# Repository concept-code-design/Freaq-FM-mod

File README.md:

# An interpretation of the Meebleeps / Wirehead Freaq FM Synth
## Arduino Synth with Dual-voice 2-OP FM | Generative 2-track Polymetric Sequencer | Mozzi SDK

## NOTE This code is an open-source prototype and is not compatible with the Wirehead Instruments version of Freaq FM hardware
- Meebleeps was rebranded as Wirehead Instruments in 2023 to avoid brand confusion with MeeBlip - another completely separate synth design company.

This interpretation is based on https://github.com/Meebleeps/MeeBleeps-Freaq-FM-Synth

It uses a different PCB with slightly different layout. It features dual independent 2-operator FM voices paired with a 2-track generative sequencer.  

Each voice has independent carrier & modulator waveforms, FM ratio, modulation envelope & LFO.

Both tracks share the a single pattern (inspired by the Intellijel Metropolix) and can be stacked in unison or have different polymetric step-counts.  Track 1 can be offset 0-3 octaves above track 2 for separate bass & lead.

The code was addressed by Claude to match my hardware. It now also includes working MIDI out.

 #### Source Code:      https://github.com/Meebleeps/MeeBleeps-Freaq-FM-Synth
 #### Youtube Demo:     https://www.youtube.com/watch?v=KD6IrcmMkoA
 #### Youtube Channel:  https://www.youtube.com/channel/UC4I1ExnOpH_GjNtm7ZdWeWA

Source released under Creative Commons Attribution-NonCommercial-ShareAlike 4.0
Copyright (C) 2026 Concept & Code

***

## Important build-notes 

- My pcb has normally-open switches
- Work and Compile PlatformIO (I use VSCodium)). 

***

## Voices

-   2 independent FM voices
-   2-operator FM (for old-school prince of persia vibes! 😂)
-   Multi-mode FM ratios - quantised, free-multiple, independent
-   Multiple operator waveforms for carrier & modulator - Sine, Saw, Reverse Saw, Square, Noise, Off
-   Modulation level controlled by Attack/Decay envelope and LFO per-voice
-   Multiple LFO waveforms (same tables as the carrier oscillators) Sine, Saw, Reverse Saw, Square, Noise

## Sequencer

-   2/1.5 track polymetric sequencer with up to 16 steps per track (Both tracks use same note sequence but can have different step-counts for polymetric phasing)
-   Multiple generative algorithms - (semi)random notes, (semi)random runs, arpeggio, drone 
-   Sequence mutates/evolves at user-defined rate & note-density
-   Selectable tonic, octave & scale quantisation (Major, Minor, Pentatonic, Phrygian (GOA!), Octaves, Fifths)
-   Tap-tempo control
-   Sync input & output (Korg Volca compatible) 
-   16-step parameter-lock recording of synth parameters for track 1 (the Elektron way!)

## Hardware 
-   Arduino Nano (Elegoo) 
-   8x8 LED display with a MAX7219-based control board
-   Simple Mozzi output circuit 
-   Added power filtering caps on DC input and 5V rail
-   Designed to fit into Volca form factor 
-   Laser-cut metalisized acrylic faceplate 
-   Laser-cut wooden enclosure 
-   7V-12DC DC Power input 
-   Access to nano's USB port for firmware upgrades 

## Pins

These are the defaults in the original software:

| Pin | Function   | Name in `MutantFMSynth.ino` |
| --- | ---------- | --------------------------- |
| A0  | Mutation   | ANALOG_INPUT_MUTATION       |
| A1  | Wobble     | ANALOG_INPUT_LFO            |
| A2  | Population | ANALOG_INPUT_STEPCOUNT      |
| A3  | Attack     | ANALOG_INPUT_MOD_ENVELOPE2  |
| A4  | Lifespan   | ANALOG_INPUT_DECAY          |
| A5  | Decay      | ANALOG_INPUT_MOD_ENVELOPE1  |
| A6  | Ratio      | ANALOG_INPUT_MOD_RATIO      |
| A7  | Depth      | ANALOG_INPUT_MOD_AMOUNT     |
| D3  | Start      | BUTTON_INPUT_START          |
| D4  | Voice      | BUTTON_INPUT_VOICE          |
| D5  | Rec        | BUTTON_INPUT_REC            |
| D6  | Scales     | BUTTON_INPUT_SCALE          |
| D10 | Func       | BUTTON_INPUT_FUNC           |
| D12 | Tonic      | BUTTON_INPUT_TONIC          |

My hardware version (Romix panel)

The firmware in `src/` is configured for this panel. Knob functions are `primary / [FUNC] held`.

| Pin | Panel label            | Name in `MutantFMSynth.ino`  |
| --- | ---------------------- | ---------------------------- |
| A0  | MUTATION / density     | ANALOG_INPUT_MUTATION        |
| A1  | ATTACK / carrier       | ANALOG_INPUT_MOD_ENVELOPE2   |
| A2  | AMP DECAY / octave     | ANALOG_INPUT_DECAY           |
| A3  | SEQ LENGTH             | ANALOG_INPUT_STEPCOUNT       |
| A4  | DECAY / mod            | ANALOG_INPUT_MOD_ENVELOPE1   |
| A5  | FM RATIO / mode        | ANALOG_INPUT_MOD_RATIO       |
| A6  | DEPTH / lfo            | ANALOG_INPUT_MOD_AMOUNT      |
| A7  | LFO DEPTH / lfo rate   | ANALOG_INPUT_LFO             |
| D12 | Start                  | BUTTON_INPUT_START           |
| D5  | Voice                  | BUTTON_INPUT_VOICE           |
| D4  | Rec                    | BUTTON_INPUT_REC             |
| D10 | Scale                  | BUTTON_INPUT_SCALE           |
| D3  | Func                   | BUTTON_INPUT_FUNC            |
| D6  | Algo                   | BUTTON_INPUT_ALGO            |

Hardware notes:

- The switches are normally open and short their pin to GND (`SWITCH_TYPE_NORMALLY_CLOSED` is off in `MutantFMSynthOptions.h`).
- D10 (Scale) and D12 (Start) are the ATmega328's hardware SPI SS and MISO pins. With the SPI enabled, a Scale press drops it into slave mode and the Start LED can't be driven, so the display is driven by bit-banged SPI on D11 (data), D13 (clock) and D7 (CS) instead (`LedMatrix.cpp`).
- Display test: `pio run -e displaytest -t upload` walks a single pixel along rows 1–8, left to right. Flash the synth again with `pio run -t upload`.
- Button LEDs (`ENABLE_BUTTON_LEDS`): every Nano pin is in use, so each LED shares its button's pin. Wire the LED as +5V → 470Ω → LED → button pin (instead of → GND). The firmware lights an LED by pulling the pin low and turns it off by making the pin an input with pull-up (open-collector style, never driven high), briefly releasing all LEDs (for 100µs) every ~55ms to read the switches. A pressed switch always lights its own LED.
  - FUNC: lit while held
  - REC: lit while recording / clearing parameter locks
  - START: lit while the sequencer runs
  - VOICE: lit while voice 2 is selected
  - SCALE, ALGO: lit only while pressed
- MIDI out (`ENABLE_MIDI_OUTPUT`, on by default): notes for voice 1 on channel 1 and voice 2 on channel 2, on TX (D1) at 31250 baud to the TRS type B jack. All text output on the serial port is compiled out while it is enabled.
- `DEBUG_SERIAL_UI` in `MutantFMSynthOptions.h` prints every button and knob change at 115200 baud, for checking the wiring (only with MIDI off).
- Operation manual: [MANUAL.md](MANUAL.md).

## User Guide (Romix panel)

### Buttons

| Button | Press                               | [FUNC] + press                 |
| ------ | ----------------------------------- | ------------------------------ |
| START  | Start / stop the sequencer          | Tap tempo                      |
| SCALE  | Next scale                          | Next tonic (A–G)               |
| ALGO   | Next generative algorithm           | –                              |
| VOICE  | Select voice 1 / voice 2            | –                              |
| REC    | Hold while turning a knob to record it into the sequence (parameter lock) | Hold [FUNC][REC] while turning a knob to delete that knob's recorded locks |
| FUNC   | Hold to access the alternative functions | |

### Knobs

| Knob      | Turn                                         | [FUNC] + turn                                   |
| --------- | -------------------------------------------- | ----------------------------------------------- |
| MUTATION  | How often the sequence changes               | Density – how likely a step plays a note        |
| ATTACK    | Mod envelope attack (current voice)          | Carrier waveform (current voice)                |
| AMP DECAY | Note length (both voices)                    | Octave – voice 2 selected: base octave 0–6 (both voices follow); voice 1 selected: voice 1 plays 0–3 octaves above voice 2 |
| SEQ LEN   | Steps (1–16) for the current voice           | Steps for both voices                           |
| DECAY     | Mod envelope decay (current voice)           | Modulator waveform (current voice)              |
| FM RATIO  | FM ratio (current voice)                     | FM ratio mode (current voice)                   |
| DEPTH     | Mod envelope depth (current voice)           | LFO waveform (current voice)                    |
| LFO DEPTH | LFO depth (current voice)                    | LFO rate (current voice)                        |

Parameter locks can be recorded for ATTACK, AMP DECAY, DECAY, FM RATIO, DEPTH and LFO DEPTH and apply to voice 1.

Functions from the Wirehead v1.7 manual that this firmware does not have: control-all voice mode, voice mix / detune, LFO destinations, clock division, global settings, patch save/load and the call/response and scale algorithms.

### Original panel guide

#### Buttons

-   Tonic - Select tonic through natural notes A - G
    -   [Func] + Scale - Shift base octave from 0 - 5
    -   [Func][Rec] + Scale - Select octave offset to Track 1 (track 1 & 2 can be 0-4 octaves apart)
-   Scales - Select current musical scale
    -   [Func] + Algo - Select current generative algorithm
    -   [Func][Rec] + Algo - Select the LFO waveform for the current voice 
-   Rec + knob - Hold down while moving a knob to record those parameters to the sequence 
    -   [Rec] + knob - Hold down while moving a knob to delete the recorded sequence for that parameter 
    -   [Func] + buttons - Access various secondary functions
-   Start - Start or stop the sequencer
    -   [Func] + Start - Tap tempo
    -   [Func][Rec] + Start - Select the MODULATOR waveform for the current voice 
-   Voice - Select the active track which can be edited using the parameter inputs
    -   [Func] + Voice - Select the FM ratio mode for the current voice
    -   [Func][Rec] + Voice - Select CARRIER Waveform for the current voice 

#### Rotary Inputs

-   Mutation - Adjust the likelihood that the sequence will change over time
    -   [Func] + Mutation - Adjust the liklihood that any given step will be a note or a rest
-   Population - Adjust the number of steps for the active track
    -   [Func] + Population - Adjust the number of steps for all tracks
-   Lifespan - Adjust the length of the notes (for all tracks)
-   Ratio - Select the carrier--to-modulator FM ratio (based on the current FM mode)
-   Wobble - Adjust the amount of LFO to apply to the modulator level for the active track
    -   [Func] + Wobble - Adjust the LFO rate for the active track
-   Attack - Adjust the attack time for the modulator level envelope
-   Decay - Adjust the decay time for the modulator level envelope
-   Depth - Adjust the amount of envelope to apply to the modulator level for the active track

## Issues / Limitations

-   Fair bit of jitter in the sequencer timing when tracking external sync due to somewhat naive approach to the 2-step-per-pulse volca sync 
-   Mozzi audio library has 10ms buffer 
-   The code is written for NORMALLY CLOSED switches - see latest updates in MutantFMSynth.ino updateButtonControls() for support for NORMALLY OPEN
-   The code may not fit in the Arduino Nano when compiled using the Arduino IDE or using different bootloaders

### Compiling on the Arduino IDE

If you have issues with the compiled size not fitting in the Nano, this may be due to different compiler (I use VSCode & PlatformIO) or different bootloader in the Arduino (not sure which I have, but am compiling to Elegoo brand arduino nano). 
- Check the compiler options in **MutantFMSynthOptions.h** to alter switch type or compile size
- open the file MutantFMSynthOptions.h
- find the line: //#define COMPILE_SMALLER_BINARY
- uncomment the line so it looks like this:  #define COMPILE_SMALLER_BINARY
- Then compile. It should now easily fit into the Nano.  This omits the semi-random wave tablesbut you probably won't miss it! :)

### Compiling in VSCode / PlatformIO

- Do not install the Mozzi library from PlatformIO in VSCode, it's outdated and will not build successfully. Instead, install its [latest git master branch](https://github.com/sensorium/Mozzi) to `lib/mozzi`. 
- The default settings target the Nano ATmega328 with the new bootloader. If you have avrdude errors during upload, you might have the old bootloader: change both instances of `nanoatmega328new` to `nanoatmega328` in `plaformio.ini`.

## Thanks

-   Inspired by Hagiwo's modular builds: https://www.youtube.com/channel/UCxErrnnVNEAAXPZvQFwobQw 
-   Mozzi audio library: https://sensorium.github.io/Mozzi/ 
-   Inkscape for vector graphics: https://inkscape.org/ 
-   Laser-cutting by Perth Creative Industries https://www.pcilasercutting.com.au/
-   Fritzing for circuit design: https://fritzing.org/ 
-   Great Scott for electronics tips! https://www.youtube.com/channel/UC6mIxFTvXkWQVEHPsEdflzQ

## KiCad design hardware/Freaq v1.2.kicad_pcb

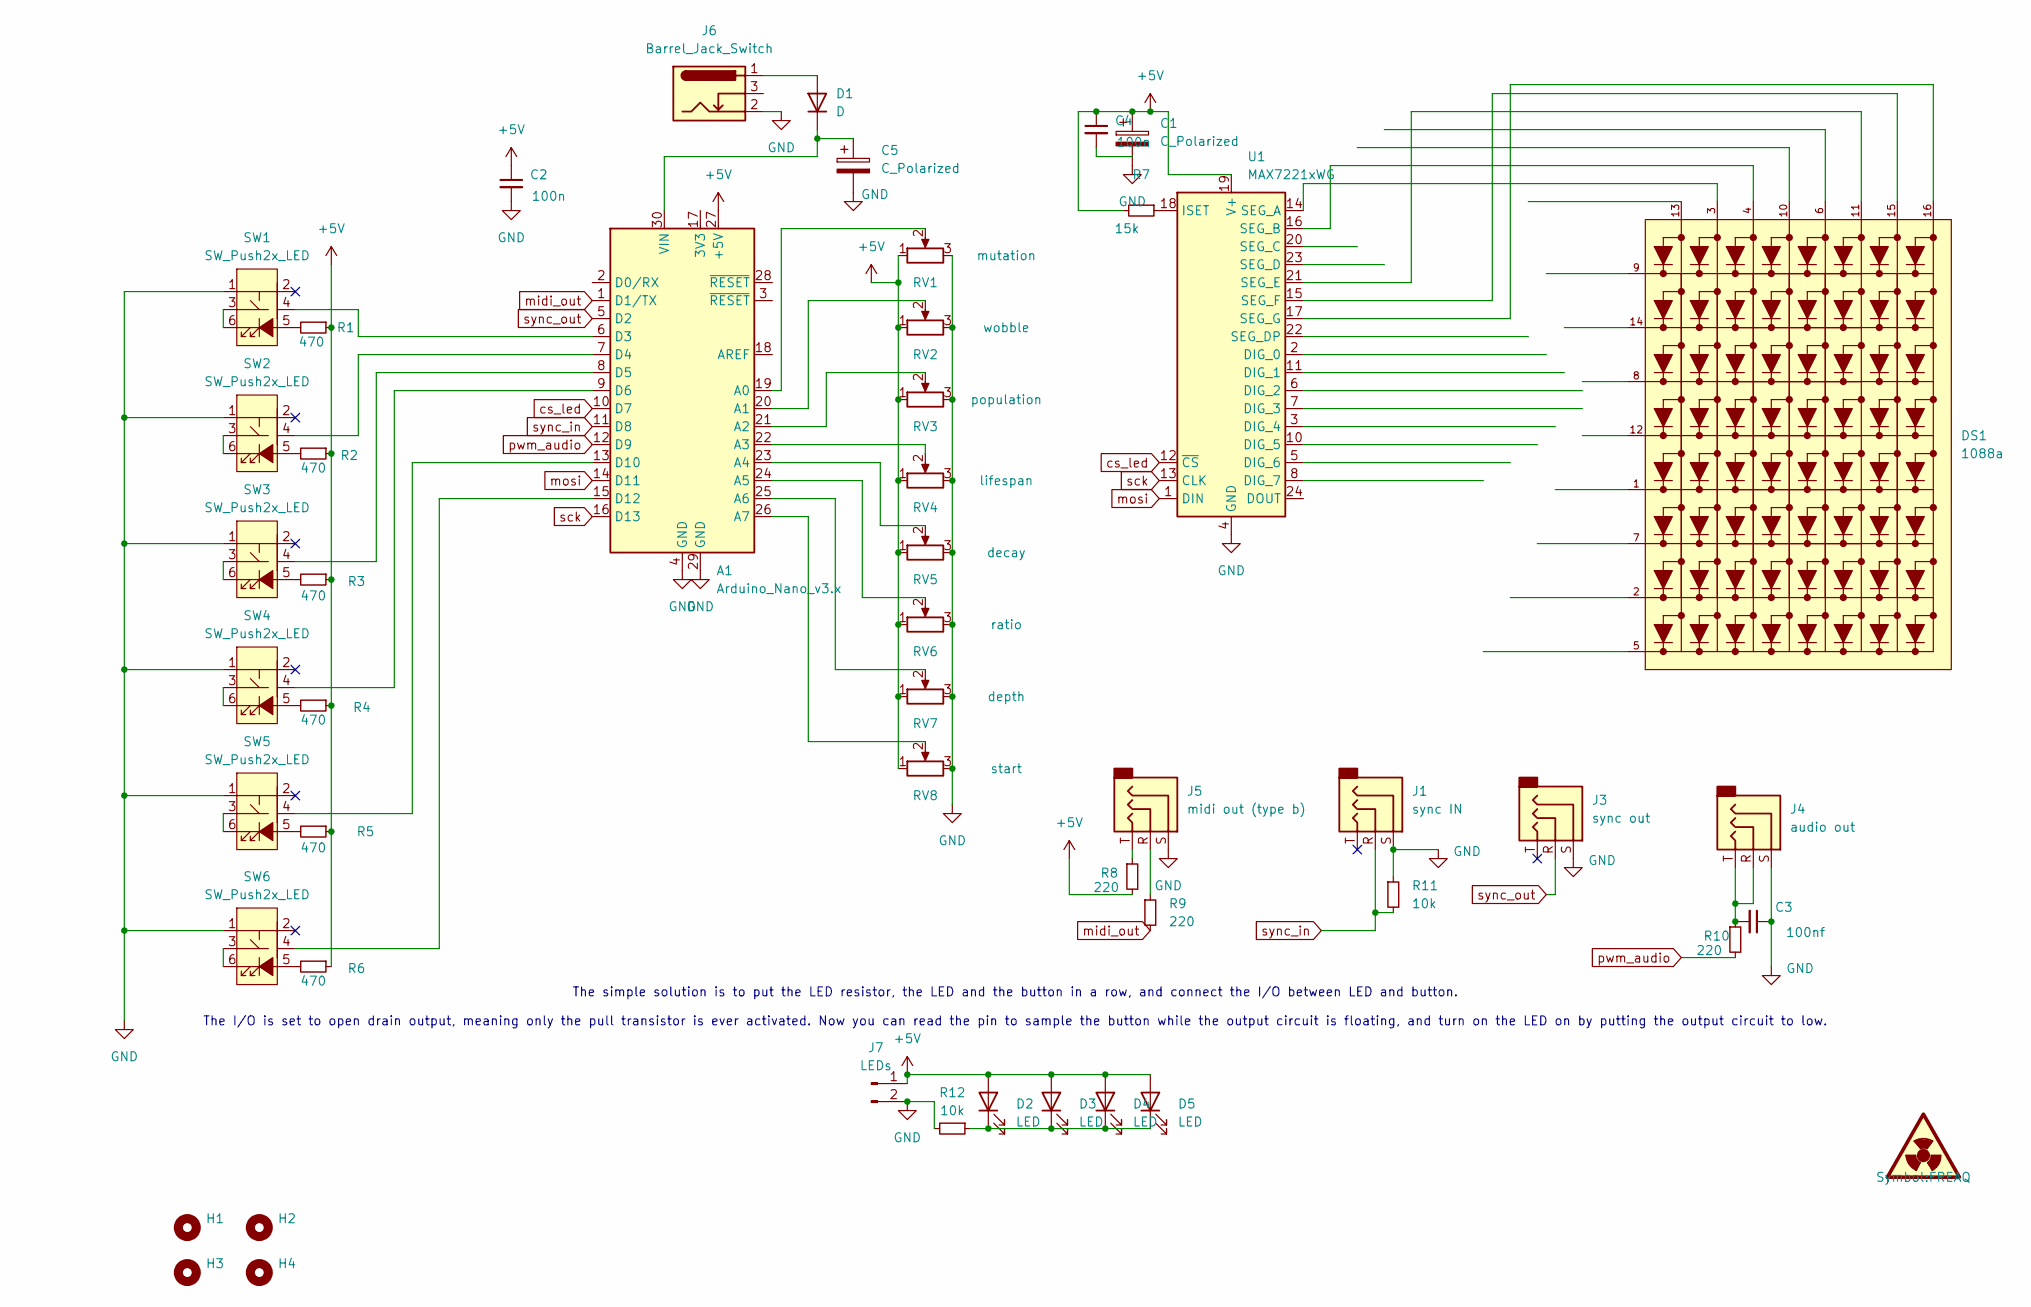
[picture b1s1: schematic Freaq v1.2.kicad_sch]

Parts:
A1: Arduino_Nano_v3.x; Arduino_Nano
C1, C5: C_Polarized; CP_Elec_8x6.5
C2, C4: 100n; C_1206_3216Metric_Pad1.33x1.80mm_HandSolder
C3: 100nf; C_1206_3216Metric_Pad1.33x1.80mm_HandSolder
D1: D; D_SMB
D2, D3, D4, D5: LED; LED_0805_2012Metric
DS1: 1088a; DISPLAY_1088a; PARTREV V.11A
H1, H2, H3, H4: MountingHole; MountingHole_3.2mm_M3
J1: sync IN; Jack_3.5mm_PJ320D_Horizontal
J3: sync out; Jack_3.5mm_PJ320D_Horizontal
J4: audio out; Jack_3.5mm_PJ320D_Horizontal
J5: midi out (type b); Jack_3.5mm_PJ320D_Horizontal
J6: Barrel_Jack_Switch; BarrelJack_3.5mm_Ali
J7: LEDs; PinHeader_1x02_P2.54mm_Horizontal
R1, R2, R3, R4, R5, R6: 470; R_1206_3216Metric_Pad1.30x1.75mm_HandSolder
R7: 15k; R_1206_3216Metric_Pad1.30x1.75mm_HandSolder
R8, R9, R10: 220; R_1206_3216Metric_Pad1.30x1.75mm_HandSolder
R11, R12: 10k; R_1206_3216Metric_Pad1.30x1.75mm_HandSolder
RV1: mutation; Pot_Alpha_RD901F-ALI
RV2: wobble; Pot_Alpha_RD901F-ALI
RV3: population; Pot_Alpha_RD901F-ALI
RV4: lifespan; Pot_Alpha_RD901F-ALI
RV5: decay; Pot_Alpha_RD901F-ALI
RV6: ratio; Pot_Alpha_RD901F-ALI
RV7: depth; Pot_Alpha_RD901F-ALI
RV8: start; Pot_Alpha_RD901F-ALI
SW1, SW2, SW3, SW4, SW5, SW6: SW_Push2x_LED; SW_PUSH-12mm_LED
U1: MAX7221xWG; SOIC-24W_7.5x15.4mm_P1.27mm

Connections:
+5V: A1.27 (+5V), C1.1, C2.1, C4.1, D2.2 (A), D3.2 (A), D4.2 (A), D5.2 (A), J7.1, R1.1, R2.1, R3.1, R4.1, R5.1, R6.1, R7.2, R8.2, RV1.1, RV2.1, RV3.1, RV4.1, RV5.1, RV6.1, RV7.1, RV8.1, U1.19 (V+)
GND: A1.4 (GND), A1.29 (GND), C1.2, C2.2, C3.1, C5.2, J1.S, J3.S, J4.S, J5.S, J6.2, J7.2, R11.1, R12.2, RV1.3, RV2.3, RV3.3, RV4.3, RV5.3, RV6.3, RV7.3, RV8.3, SW1.1, SW2.1, SW3.1, SW4.1, SW5.1, SW6.1, U1.4 (GND), U1.9 (GND)
unnamed: A1.19 (A0), RV1.2
unnamed: A1.20 (A1), RV2.2
unnamed: A1.21 (A2), RV3.2
unnamed: A1.22 (A3), RV4.2
unnamed: A1.23 (A4), RV5.2
unnamed: A1.24 (A5), RV6.2
unnamed: A1.25 (A6), RV7.2
unnamed: A1.26 (A7), RV8.2
unnamed: A1.6 (D3), SW1.4 (2)
unnamed: A1.7 (D4), SW2.4 (2)
unnamed: A1.8 (D5), SW3.4 (2)
unnamed: A1.9 (D6), SW4.4 (2)
unnamed: A1.13 (D10), SW5.4 (2)
unnamed: A1.15 (D12), SW6.4 (2)
unnamed: A1.30 (VIN), C5.1, D1.1 (K)
unnamed: C3.2, J4.R, J4.T, R10.1
unnamed: D1.2 (A), J6.1
unnamed: D2.1 (K), D3.1 (K), D4.1 (K), D5.1 (K), R12.1
unnamed: J5.R, R9.1
unnamed: J5.T, R8.1
unnamed: R1.2, SW1.5 (A)
unnamed: SW1.3 (1), SW1.6 (K)
unnamed: R2.2, SW2.5 (A)
unnamed: SW2.3 (1), SW2.6 (K)
unnamed: R3.2, SW3.5 (A)
unnamed: SW3.3 (1), SW3.6 (K)
unnamed: R4.2, SW4.5 (A)
unnamed: SW4.3 (1), SW4.6 (K)
unnamed: R5.2, SW5.5 (A)
unnamed: SW5.3 (1), SW5.6 (K)
unnamed: R6.2, SW6.5 (A)
unnamed: SW6.3 (1), SW6.6 (K)
unnamed: DS1.9, U1.2 (DIG_0)
unnamed: DS1.14, U1.11 (DIG_1)
unnamed: DS1.8, U1.6 (DIG_2)
unnamed: DS1.12, U1.7 (DIG_3)
unnamed: DS1.1, U1.3 (DIG_4)
unnamed: DS1.7, U1.10 (DIG_5)
unnamed: DS1.2, U1.5 (DIG_6)
unnamed: DS1.5, U1.8 (DIG_7)
unnamed: R7.1, U1.18 (ISET)
unnamed: DS1.3, U1.14 (SEG_A)
unnamed: DS1.4, U1.16 (SEG_B)
unnamed: DS1.10, U1.20 (SEG_C)
unnamed: DS1.6, U1.23 (SEG_D)
unnamed: DS1.13, U1.22 (SEG_DP)
unnamed: DS1.11, U1.21 (SEG_E)
unnamed: DS1.15, U1.15 (SEG_F)
unnamed: DS1.16, U1.17 (SEG_G)
cs_led: A1.10 (D7), U1.12 (~CS)
midi_out: A1.1 (D1/TX), R9.2
mosi: A1.14 (D11), U1.1 (DIN)
pwm_audio: A1.12 (D9), R10.2
sck: A1.16 (D13), U1.13 (CLK)
sync_in: A1.11 (D8), J1.R, R11.2
sync_out: A1.5 (D2), J3.R

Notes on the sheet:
The simple solution is to put the LED resistor, the LED and the button in a row, and connect the I/O between LED and button. The I/O is set to open drain output, meaning only the pull transistor is ever activated. Now you can read the pin to sample the button while the output circuit is floating, a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

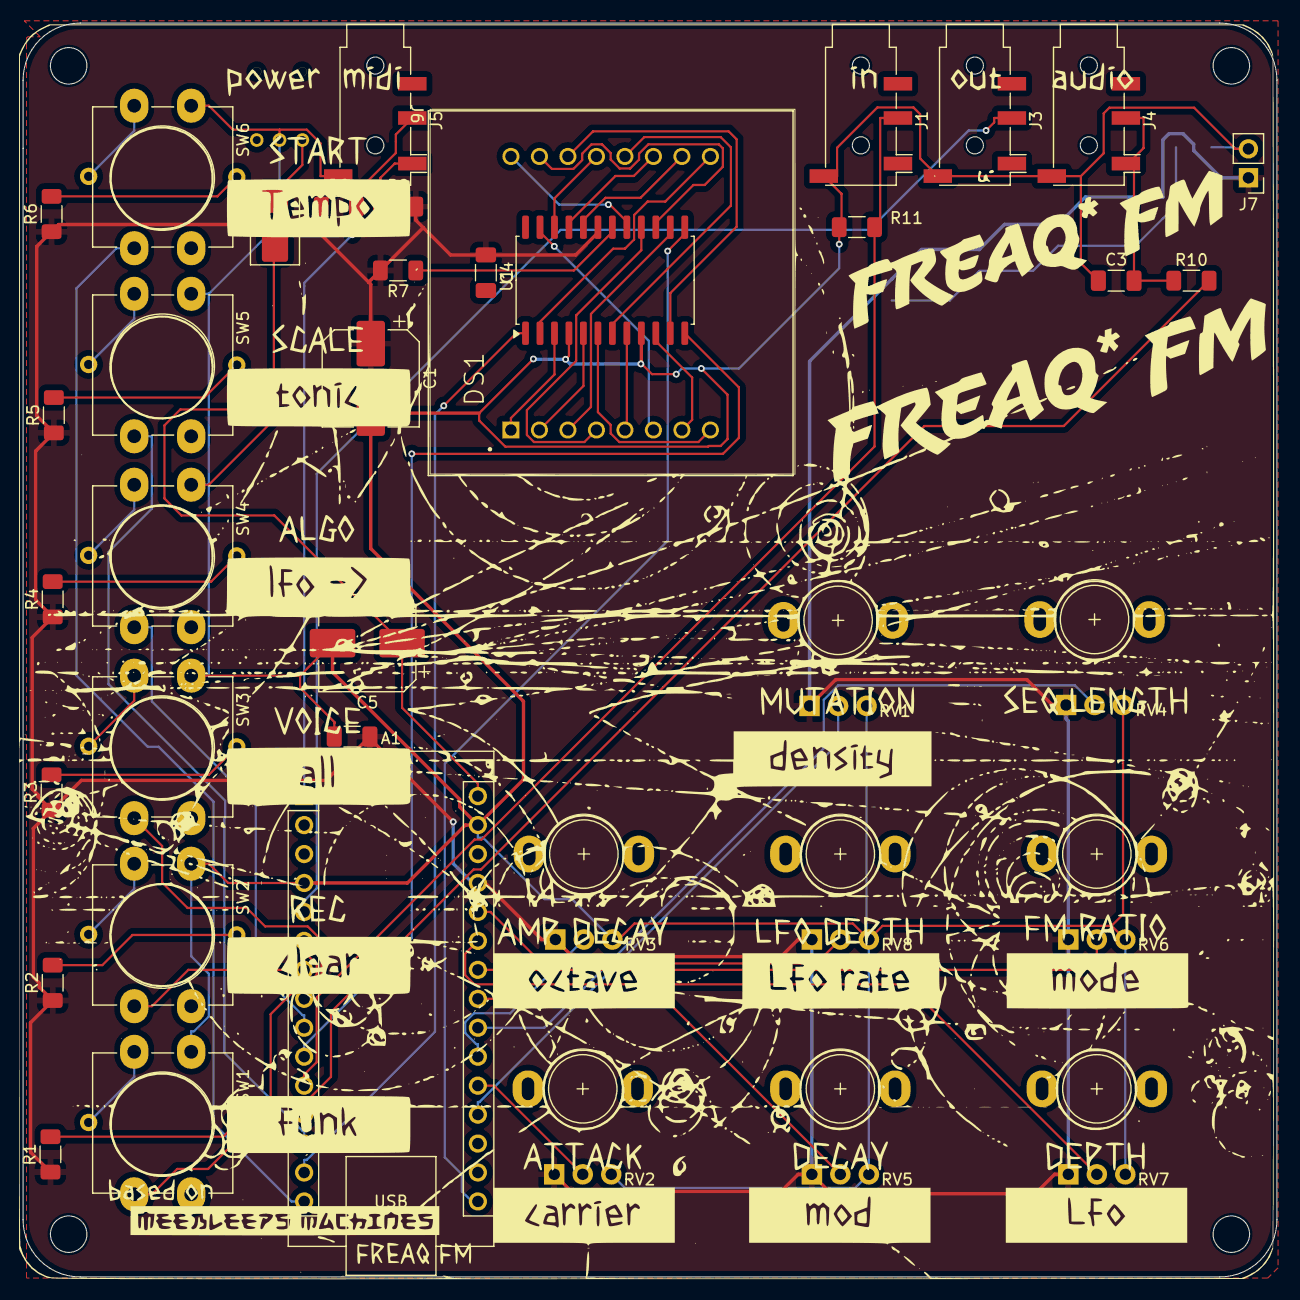
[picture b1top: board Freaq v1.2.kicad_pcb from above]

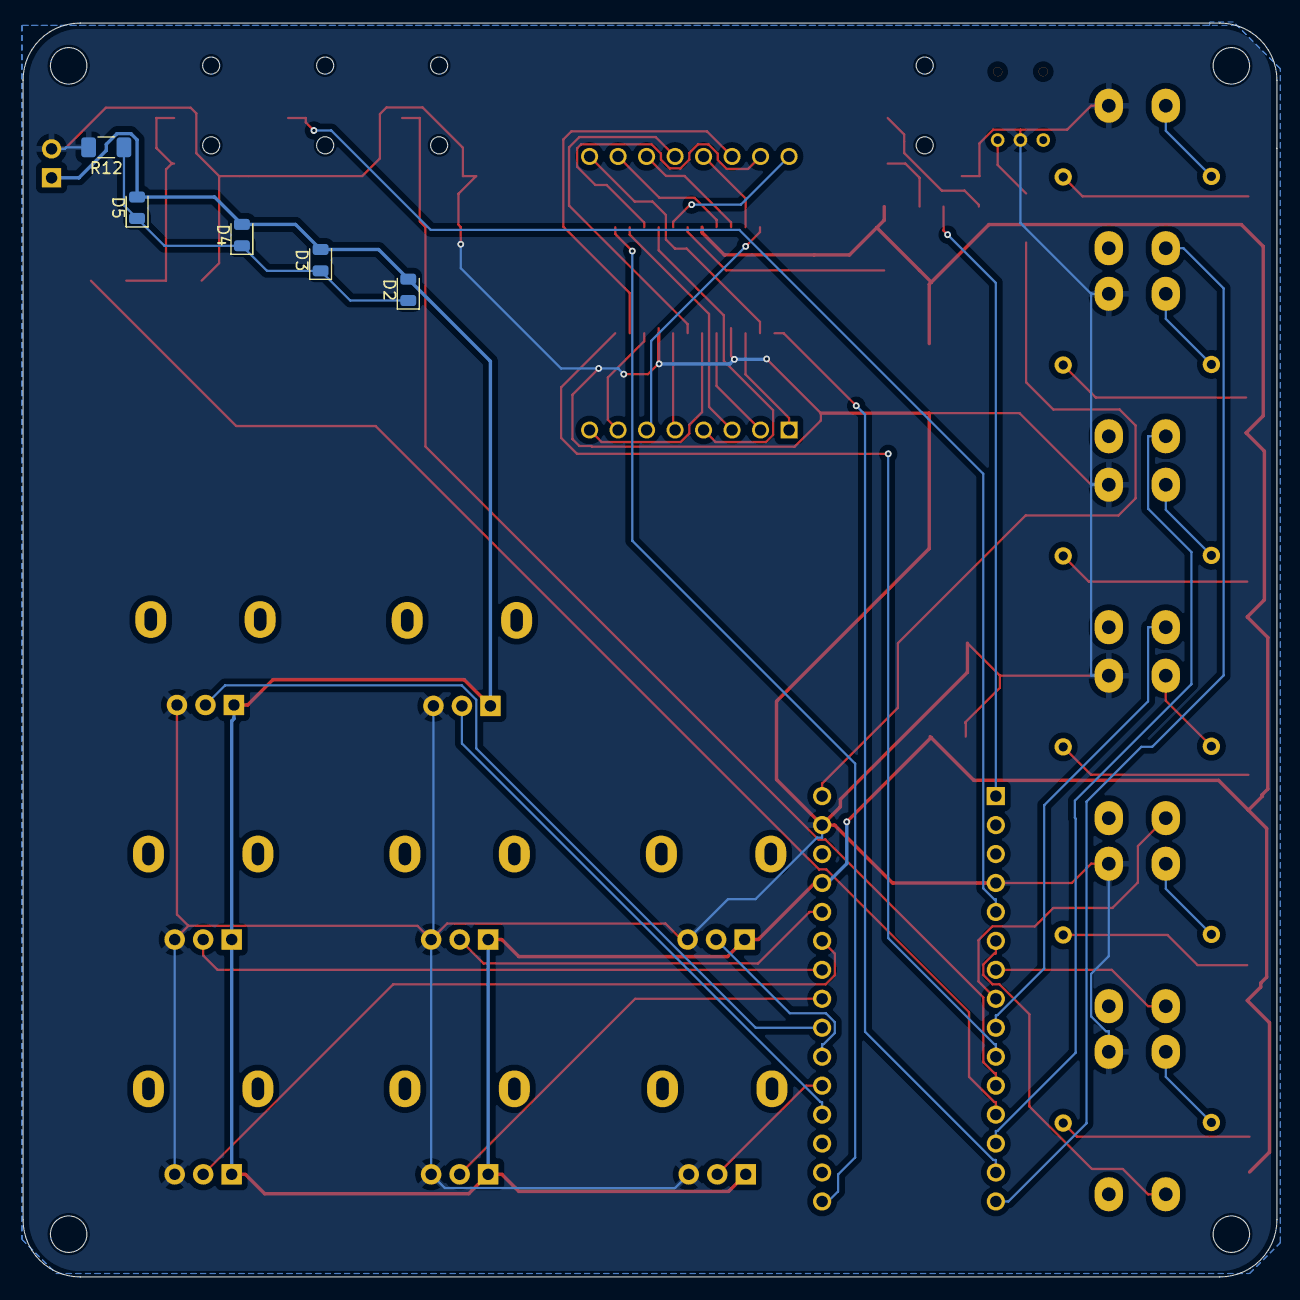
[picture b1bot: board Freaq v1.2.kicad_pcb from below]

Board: 2 copper layers, 110.0 x 110.0 mm, 51 parts (5 on the bottom side), 57 nets.

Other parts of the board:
FREAQ_brd: FREAQ name
FREAQ_panel: FREAQ* non neg

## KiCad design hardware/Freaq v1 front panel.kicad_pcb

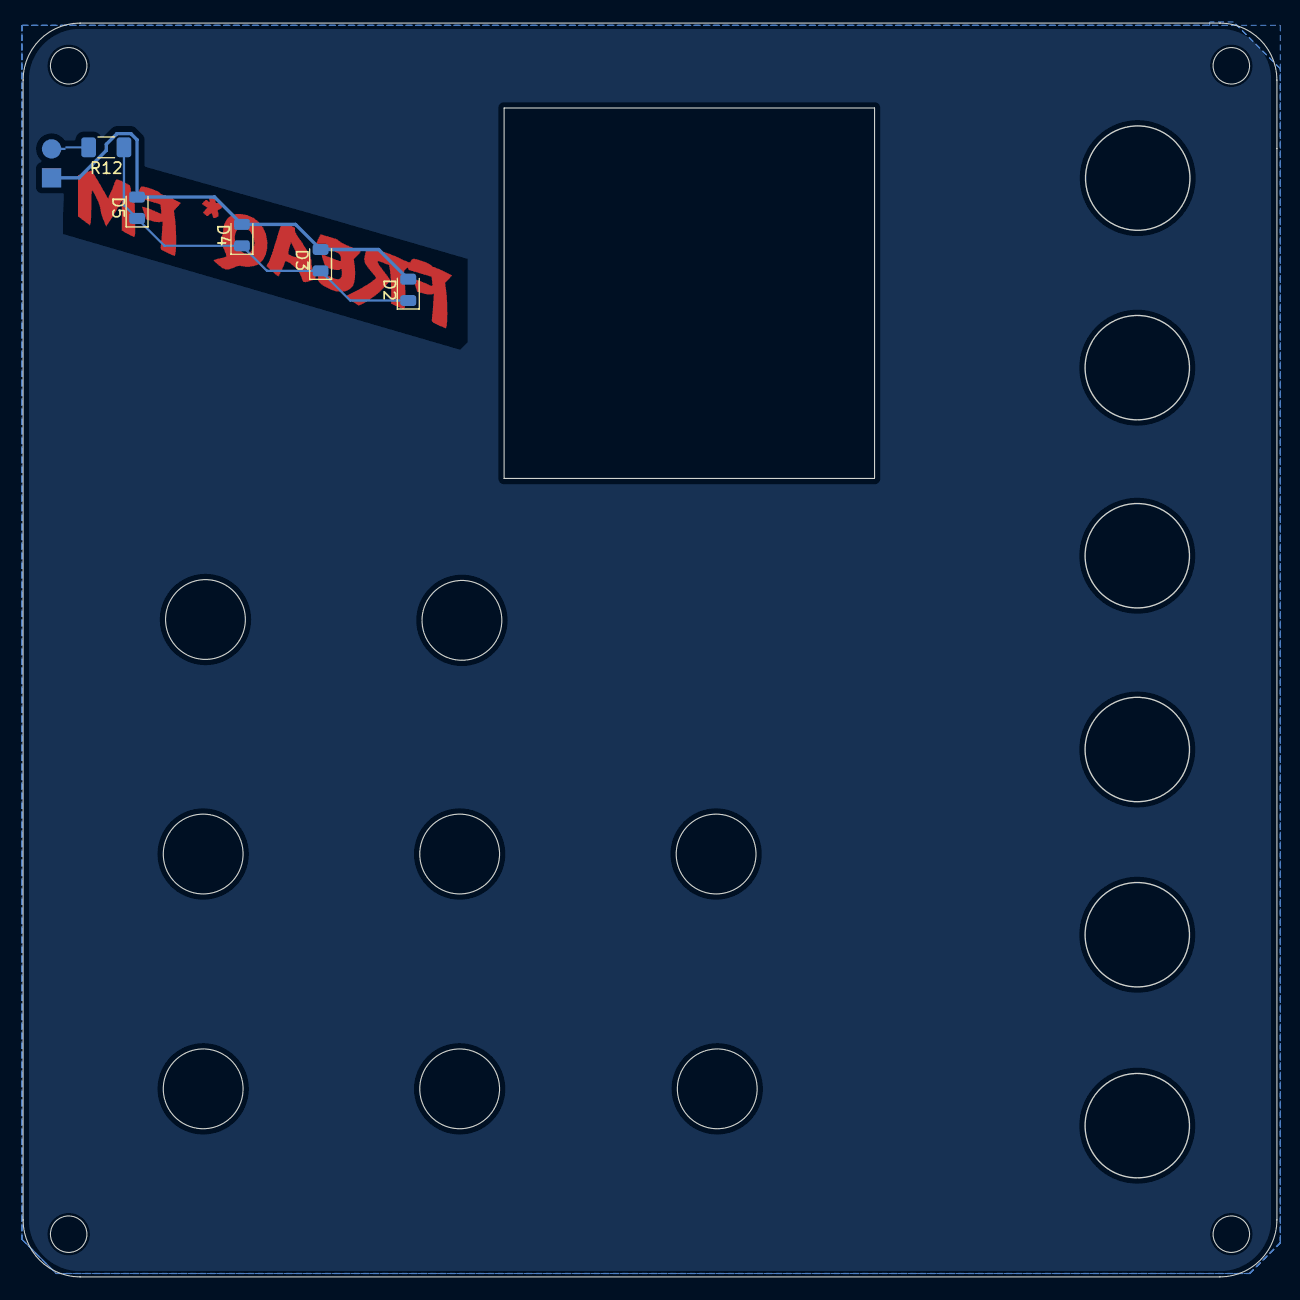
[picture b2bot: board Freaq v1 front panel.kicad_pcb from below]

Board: 2 copper layers, 110.0 x 110.0 mm, 27 parts (5 on the bottom side), 3 nets.

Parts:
D2, D3, D4, D5: LED; LED_0805_2012Metric
DS1: 1088a; DISPLAY_1088a
FREAQ_panel: FREAQ* non neg
Fcop: freaq copper
H1, H2, H3, H4: MountingHole; MountingHole_3.2mm_M3
J7: LEDs; PinHeader_1x02_P2.54mm_Vertical
R12: 10k; R_1206_3216Metric_Pad1.30x1.75mm_HandSolder
RV1: mutation; Pot_Alpha_RD901F-ALI-hole
RV2: wobble; Pot_Alpha_RD901F-ALI-hole
RV3: population; Pot_Alpha_RD901F-ALI-hole
RV4: lifespan; Pot_Alpha_RD901F-ALI-hole
RV5: decay; Pot_Alpha_RD901F-ALI-hole
RV6: ratio; Pot_Alpha_RD901F-ALI-hole
RV7: depth; Pot_Alpha_RD901F-ALI-hole
RV8: start; Pot_Alpha_RD901F-ALI-hole
SW6, SW6#2, SW6#3, SW6#4, SW6#5, SW6#6: SW_Push2x_LED; SW_PUSH-12mm_LED

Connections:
+5V: D2.2 (A), D3.2 (A), D4.2 (A), D5.2 (A), J7.1
GND: J7.2, R12.2
unnamed: D2.1 (K), D3.1 (K), D4.1 (K), D5.1 (K), R12.1
